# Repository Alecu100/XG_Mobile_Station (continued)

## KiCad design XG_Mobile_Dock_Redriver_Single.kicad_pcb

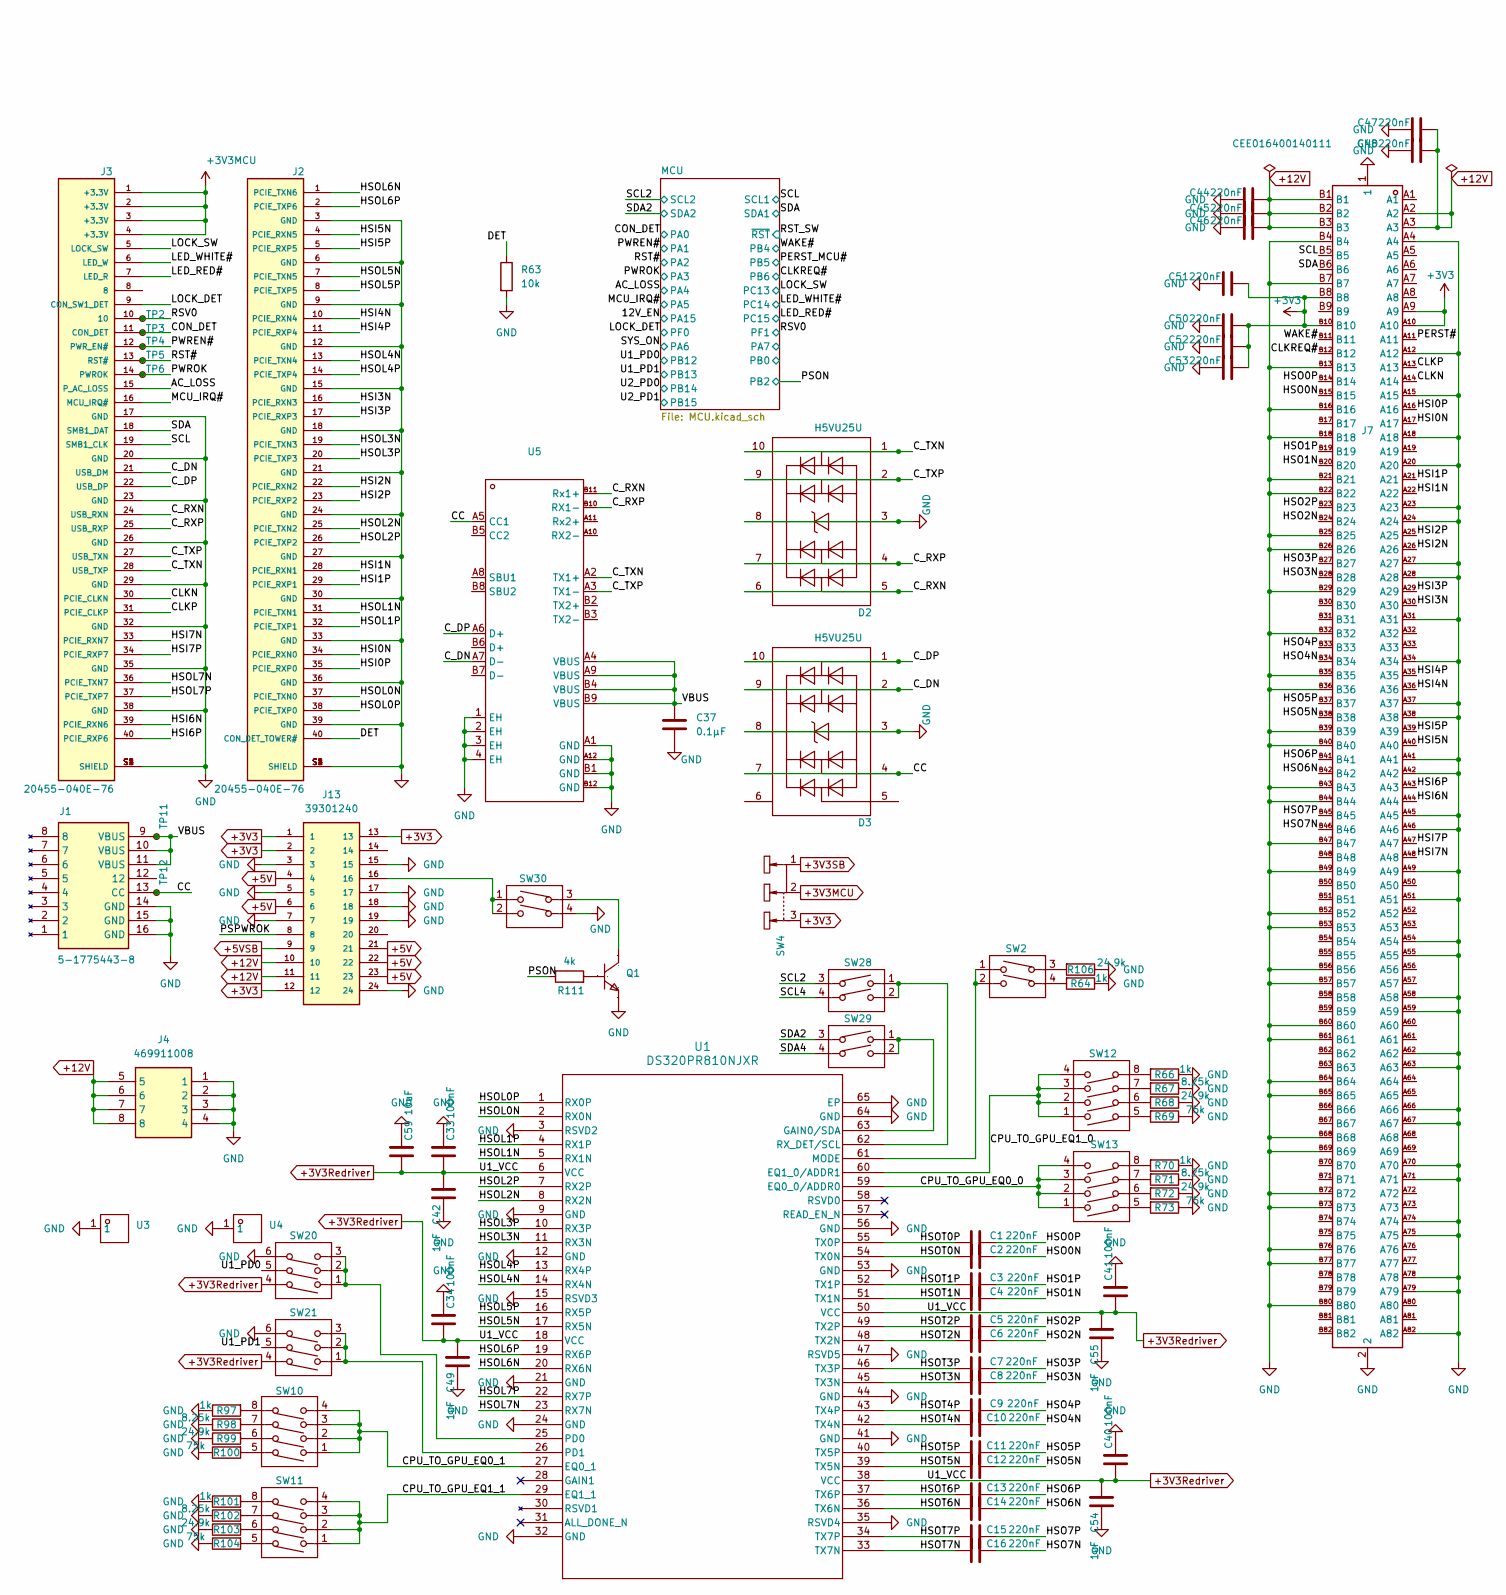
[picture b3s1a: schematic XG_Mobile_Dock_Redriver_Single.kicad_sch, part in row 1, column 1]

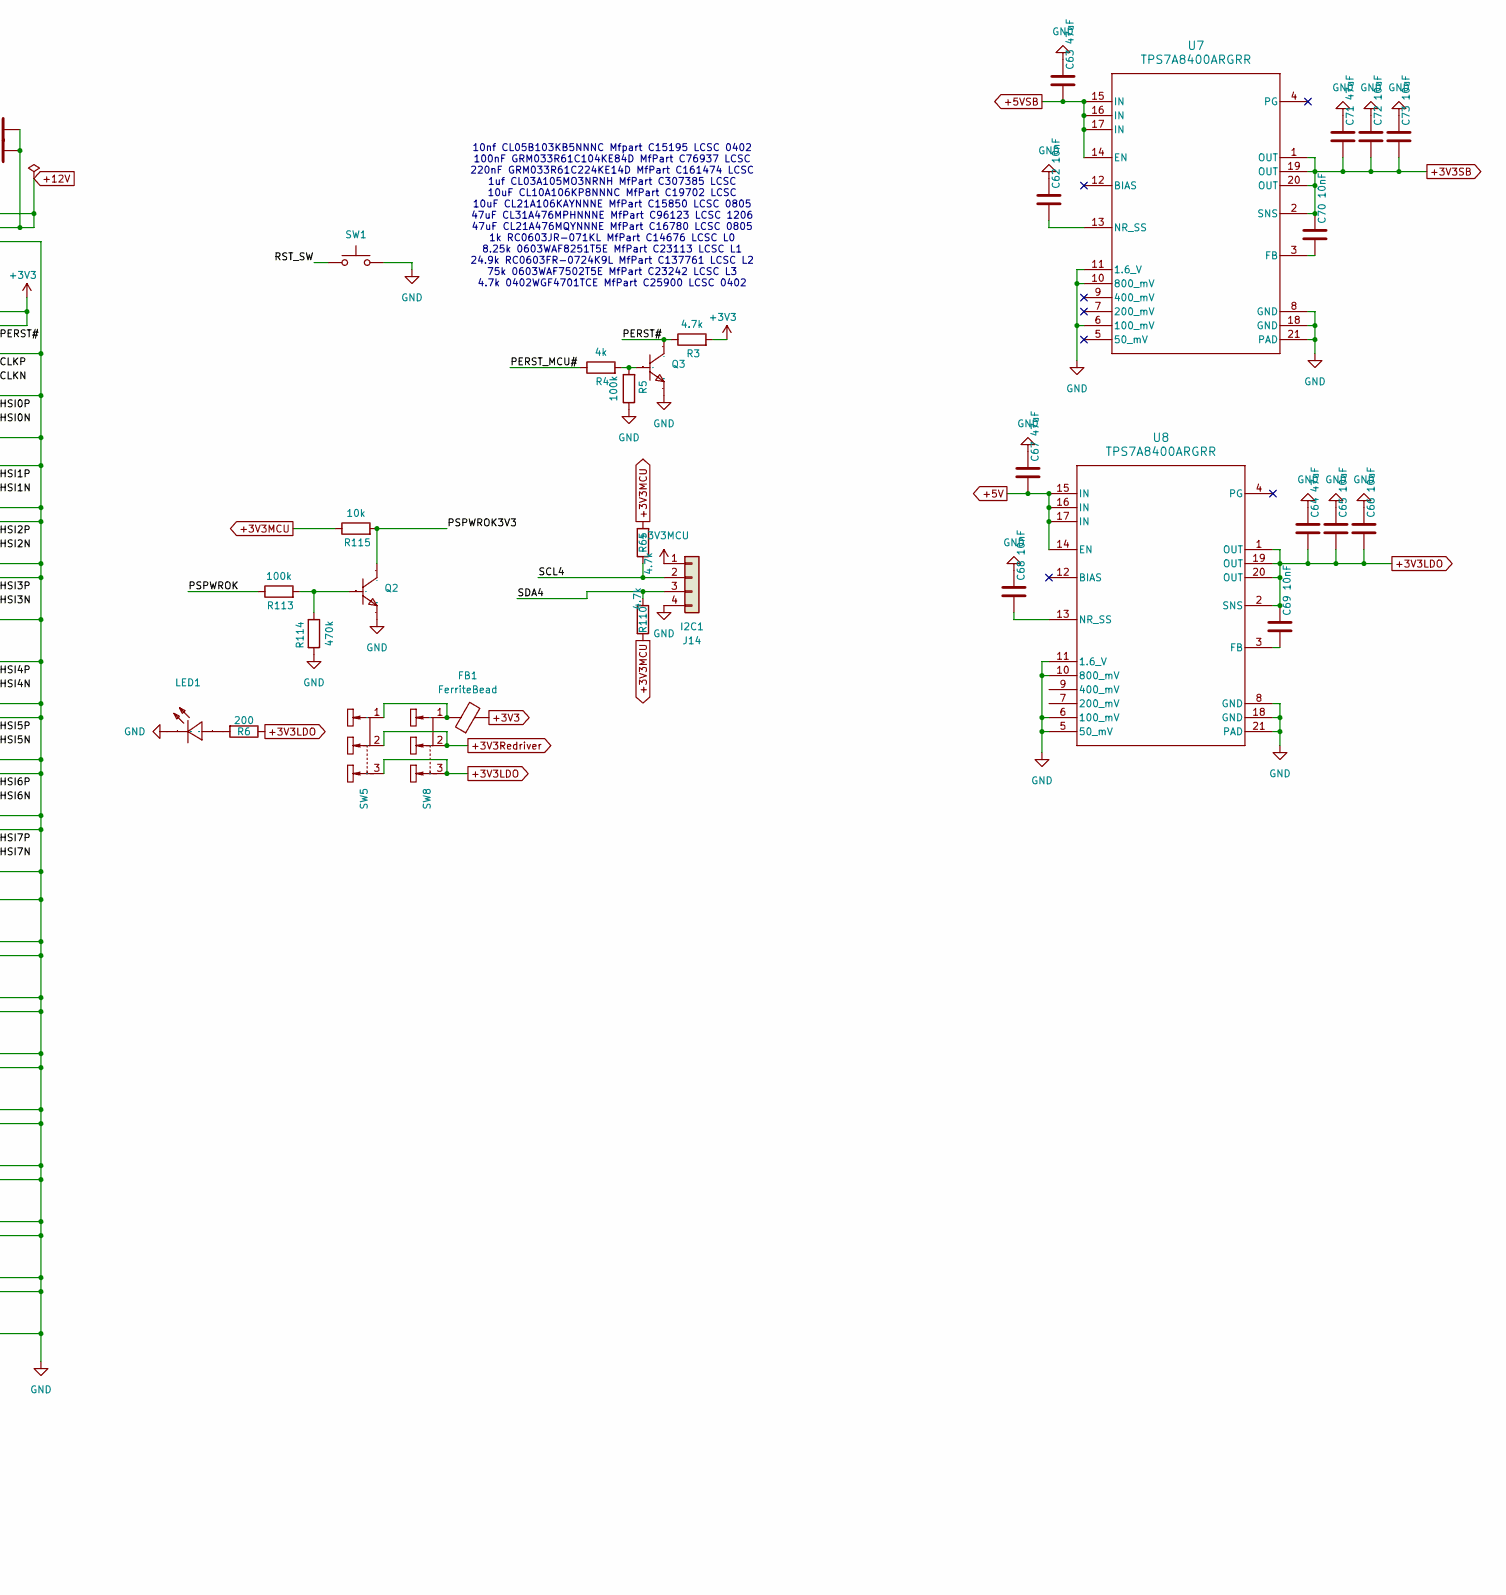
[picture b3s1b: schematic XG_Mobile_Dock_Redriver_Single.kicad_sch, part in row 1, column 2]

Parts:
C1, C2, C3, C4, C5, C6, C7, C8, C9, C10, C11, C12, C13, C14, C15, C16, C44, C45, C46, C47, C48, C50, C51, C52, C53: 220nF; C_0201_0603Metric; Part_Number GRM033R61C224KE14D; LCSC C161474
C33, C34, C40, C41: 100nF; C_0201_0603Metric; Part_Number GRM033R61C104KE84D; LCSC C76937
C37: 0.1μF; C_0402_1005Metric; Part_Number CL05B104KO5NNNC; LCSC C1525
C42, C49, C54, C55: 1uF; C_0201_0603Metric; Part_Number CL03A105MO3NRNH; LCSC C307385
C59: 10uF; C_0603_1608Metric; Part_Number CL10A106KP8NNNC; LCSC C19702
C62, C68, C69, C70: 10nF; C_0402_1005Metric; Part_Number CL05B103KB5NNNC; LCSC C15195
C63, C64, C67, C71: 47uF; C_0805_2012Metric; Part_Number CL21A476MQYNNNE; LCSC C16780
C65, C66, C72, C73: 10uF; C_0805_2012Metric; Part_Number CL21A106KAYNNNE; LCSC C15850
D2, D3: H5VU25U; AZ1045-04F; Part_Number H5VU25U; LCSC C7420374
FB1: FerriteBead; R_1206_3216Metric; Part_Number FBMJ3216HS800-TV; LCSC C2661525
J1: 5-1775443-8; Manufacturer_Part_Number 5-1775443-8
J2, J3: 20455-040E-76; Part_Number 20455-040E-76; LCSC C5160883
J4: 469911008; CON_469911008; Part_Number 469911008; LCSC C17470577
J7: CEE016400140111; CONN-SMD_164P-P1.00-CEE016400140111; PARTREV C; LCSC C4762196
J13: 39301240; CON_39300240; Part_Number 39301240; LCSC C492347
J14: I2C1; PinHeader_1x04_P2.54mm_Vertical; Part_Number 2.54-1*4; LCSC C5116483
LED1: LED0603-RD; Manufacturer Part KT-0603R; LCSC Part Name 0603 红灯 高亮
Q1, Q2, Q3: SOT-23-3_L2.9-W1.3-P1.90-LS2.4-BR; Part_Number MMBT5551(RANGE:200-300); LCSC C2145
R3, R65, R110: 4.7k; R_0402_1005Metric; Part_Number 0402WGF4701TCE; LCSC C25900
R4, R111: 4k; R_0603_1608Metric; Part_Number 0603WAF4021T5E; LCSC C23040
R5, R113: 100k; R_0603_1608Metric; Part_Number 0603WAF1003T5E; LCSC C25803
R6: 200; R_0603_1608Metric; Part_Number 0603WAF2000T5E; LCSC C8218
R63: 10k; R_0402_1005Metric; Part_Number 0402WGF1002TCE; LCSC C25744
R64, R66, R70, R97, R101: 1k; R_0603_1608Metric; Part_Number RC0603JR-071KL; LCSC C14676
R67, R71, R98, R102: 8.25k; R_0603_1608Metric; Part_Number 0603WAF8251T5E; LCSC C23113
R68, R72, R99, R103, R106: 24.9k; R_0603_1608Metric; Part_Number 0603WAF8251T5E; LCSC C137761
R69, R73, R100, R104: 75k; R_0603_1608Metric; Part_Number 0603WAF8251T5E; LCSC C23242
R114: 470k; R_0603_1608Metric; Part_Number 0603WAF4703T5E; LCSC C23178
R115: 10k; R_0603_1608Metric; Part_Number 0603WAF1002T5E; LCSC C25804
SW1: SW_Push; SW_SPST_SKQG_WithStem; Part_Number TS-1187A-B-A-B; LCSC C318884
SW2, SW28, SW29, SW30: SW-TH_DSWB02LHGET; Part_Number DSWB02LHGET; LCSC C99421
SW4, SW5, SW8: SW-TH_SS-12D10L5; Part_Number SS-12D10L5; LCSC C319012
SW10, SW11, SW12, SW13: SW-TH_DSWB04LHGET; Part_Number DSWB04LHGET; LCSC C99418
SW20, SW21: SW-TH_DSWB03LHGET; Part_Number DSWB03LHGET; LCSC C99420
TP2, TP3, TP4, TP5, TP6, TP11, TP12: TestPoint_Small; TestPoint_Pad_D1.0mm
U1: DS320PR810NJXR; WQFN-64-NJX_TEX; Part_Number DS320PR810NJXR; LCSC C6539577
U3, U4: CONN-SMD_T31000; Part_Number T31000; LCSC C481468
U5: USB-C-SMD_GT-USB-7091A; Part_Number GT-USB-7091A; LCSC C3019707
U7, U8: TPS7A8400ARGRR; RGR0020A; Part_Number TPS7A8400ARGRR; LCSC C524802

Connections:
+3V3: C50.1, C51.1, C52.1, C53.1, FB1.2, J7.A9, J7.A10, J7.B8, J7.B10, J13.1, J13.2, J13.12, J13.13, R3.2, SW4.3
+3V3LDO: C64.2, C65.2, C66.2, C69.1, R6.1, SW5.3, SW8.3, U8.1 (OUT), U8.2 (SNS), U8.19 (OUT), U8.20 (OUT)
+3V3MCU: J3.1 (+3.3V), J3.2 (+3.3V), J3.3 (+3.3V), J3.4 (+3.3V), J14.1, R65.2, R110.2, R115.1, SW4.2; also elsewhere on the board
+3V3Redriver: C33.2, C34.2, C40.2, C41.2, C42.2, C49.2, C54.2, C55.2, C59.2, SW5.2, SW8.2, SW20.4, SW21.4, U1.6 (VCC), U1.18 (VCC), U1.38 (VCC), U1.50 (VCC)
+3V3SB: C70.1, C71.2, C72.2, C73.2, SW4.1, U7.1 (OUT), U7.2 (SNS), U7.19 (OUT), U7.20 (OUT)
+5V: C67.2, J13.4, J13.6, J13.21, J13.22, J13.23, U8.14 (EN), U8.15 (IN), U8.16 (IN), U8.17 (IN)
+5VSB: C63.2, J13.9, U7.14 (EN), U7.15 (IN), U7.16 (IN), U7.17 (IN)
+12V: C44.1, C45.1, C46.1, C47.1, C48.1, J4.5, J4.6, J4.7, J4.8, J7.A2, J7.A3, J7.B1, J7.B2, J7.B3, J13.10, J13.11; also elsewhere on the board
/AC_LOSS: J3.15 (P_AC_LOSS); also elsewhere on the board
/CC: D3.4 (I/O_3), D3.7 (NC), J1.13 (CC), TP12.1, U5.A5 (CC1)
/CLKN: J3.30 (PCIE_CLKN), J7.A14
/CLKP: J3.31 (PCIE_CLKP), J7.A13
/CLKREQ#: J7.B12; also elsewhere on the board
/CON_DET: J3.11 (CON_DET), TP3.1; also elsewhere on the board
/CPU_TO_GPU_EQ0_0: SW13.1, SW13.2, SW13.3, SW13.4, U1.59 (EQ0_0/ADDR0)
/CPU_TO_GPU_EQ0_1: SW10.1, SW10.2, SW10.3, SW10.4, U1.27 (EQ0_1)
/CPU_TO_GPU_EQ1_0: SW12.1, SW12.2, SW12.3, SW12.4, U1.60 (EQ1_0/ADDR1)
/CPU_TO_GPU_EQ1_1: SW11.1, SW11.2, SW11.3, SW11.4, U1.29 (EQ1_1)
/C_DN: D3.2 (I/O_2), D3.9 (NC), J3.21 (USB_DM), U5.A7 (D-)
/C_DP: D3.1 (I/O_1), D3.10 (NC), J3.22 (USB_DP), U5.A6 (D+)
/C_RXN: D2.5 (I/O_4), D2.6 (NC), J3.24 (USB_RXN), U5.B11 (Rx1+)
/C_RXP: D2.4 (I/O_3), D2.7 (NC), J3.25 (USB_RXP), U5.B10 (RX1-)
/C_TXN: D2.1 (I/O_1), D2.10 (NC), J3.28 (USB_TXP), U5.A2 (TX1+)
/C_TXP: D2.2 (I/O_2), D2.9 (NC), J3.27 (USB_TXN), U5.A3 (TX1-)
/DET: J2.40 (CON_DET_TOWER#), R63.1
/HSI0N: J2.34 (PCIE_RXN0), J7.A17
/HSI0P: J2.35 (PCIE_RXP0), J7.A16
/HSI1N: J2.28 (PCIE_RXN1), J7.A22
/HSI1P: J2.29 (PCIE_RXP1), J7.A21
/HSI2N: J2.22 (PCIE_RXN2), J7.A26
/HSI2P: J2.23 (PCIE_RXP2), J7.A25
/HSI3N: J2.16 (PCIE_RXN3), J7.A30
/HSI3P: J2.17 (PCIE_RXP3), J7.A29
/HSI4N: J2.10 (PCIE_RXN4), J7.A36
/HSI4P: J2.11 (PCIE_RXP4), J7.A35
/HSI5N: J2.4 (PCIE_RXN5), J7.A40
/HSI5P: J2.5 (PCIE_RXP5), J7.A39
/HSI6N: J3.39 (PCIE_RXN6), J7.A44
/HSI6P: J3.40 (PCIE_RXP6), J7.A43
/HSI7N: J3.33 (PCIE_RXN7), J7.A48
/HSI7P: J3.34 (PCIE_RXP7), J7.A47
/HSO0N: C2.1, J7.B15
/HSO0P: C1.1, J7.B14
/HSO1N: C4.1, J7.B20
/HSO1P: C3.1, J7.B19
/HSO2N: C6.1, J7.B24
/HSO2P: C5.1, J7.B23
/HSO3N: C8.1, J7.B28
/HSO3P: C7.1, J7.B27
/HSO4N: C10.1, J7.B34
/HSO4P: C9.1, J7.B33
/HSO5N: C12.1, J7.B38
/HSO5P: C11.1, J7.B37
/HSO6N: C14.1, J7.B42
/HSO6P: C13.1, J7.B41
/HSO7N: C16.1, J7.B46
/HSO7P: C15.1, J7.B45
/HSOL0N: J2.37 (PCIE_TXN0), U1.2 (RX0N)
/HSOL0P: J2.38 (PCIE_TXP0), U1.1 (RX0P)
/HSOL1N: J2.31 (PCIE_TXN1), U1.5 (RX1N)
/HSOL1P: J2.32 (PCIE_TXP1), U1.4 (RX1P)
/HSOL2N: J2.25 (PCIE_TXN2), U1.8 (RX2N)
/HSOL2P: J2.26 (PCIE_TXP2), U1.7 (RX2P)
/HSOL3N: J2.19 (PCIE_TXN3), U1.11 (RX3N)
/HSOL3P: J2.20 (PCIE_TXP3), U1.10 (RX3P)
/HSOL4N: J2.13 (PCIE_TXN4), U1.14 (RX4N)
/HSOL4P: J2.14 (PCIE_TXP4), U1.13 (RX4P)
/HSOL5N: J2.7 (PCIE_TXN5), U1.17 (RX5N)
/HSOL5P: J2.8 (PCIE_TXP5), U1.16 (RX5P)
/HSOL6N: J2.1 (PCIE_TXN6), U1.20 (RX6N)
/HSOL6P: J2.2 (PCIE_TXP6), U1.19 (RX6P)
/HSOL7N: J3.36 (PCIE_TXN7), U1.23 (RX7N)
/HSOL7P: J3.37 (PCIE_TXP7), U1.22 (RX7P)
/HSOT0N: C2.2, U1.54 (TX0N)
/HSOT0P: C1.2, U1.55 (TX0P)
/HSOT1N: C4.2, U1.51 (TX1N)
/HSOT1P: C3.2, U1.52 (TX1P)
/HSOT2N: C6.2, U1.48 (TX2N)
/HSOT2P: C5.2, U1.49 (TX2P)
/HSOT3N: C8.2, U1.45 (TX3N)
/HSOT3P: C7.2, U1.46 (TX3P)
/HSOT4N: C10.2, U1.42 (TX4N)
/HSOT4P: C9.2, U1.43 (TX4P)
/HSOT5N: C12.2, U1.39 (TX5N)
/HSOT5P: C11.2, U1.40 (TX5P)
/HSOT6N: C14.2, U1.36 (TX6N)
/HSOT6P: C13.2, U1.37 (TX6P)
/HSOT7N: C16.2, U1.33 (TX7N)
/HSOT7P: C15.2, U1.34 (TX7P)
/LED_RED#: J3.7 (LED_R); also elsewhere on the board
/LED_WHITE#: J3.6 (LED_W); also elsewhere on the board
/LOCK_DET: J3.9 (CON_SW1_DET); also elsewhere on the board
/LOCK_SW: J3.5 (LOCK_SW); also elsewhere on the board
/MCU_IRQ#: J3.16 (MCU_IRQ#); also elsewhere on the board
/PERST#: J7.A11, Q3.3 (C), R3.1
/PERST_MCU#: R4.1; also elsewhere on the board
/PSON: R111.1; also elsewhere on the board
/PSPWROK: J13.8, R113.1
/PSPWROK3V3: Q2.3 (C), R115.2
/PWREN#: J3.12 (PWR_EN#), TP4.1; also elsewhere on the board
/PWROK: J3.14 (PWROK), TP6.1; also elsewhere on the board
/RST#: J3.13 (RST#), TP5.1; also elsewhere on the board
/RST_SW: SW1.1; also elsewhere on the board
/RSV0: J3.10, TP2.1; also elsewhere on the board
/SCL: J3.19 (SMB1_CLK), J7.B5; also elsewhere on the board
/SCL2: SW28.3; also elsewhere on the board
/SCL4: J14.2, R65.1, SW28.4
/SDA: J3.18 (SMB1_DAT), J7.B6; also elsewhere on the board
/SDA2: SW29.3; also elsewhere on the board
/SDA4: J14.3, R110.1, SW29.4
/U1_PD0: SW20.5; also elsewhere on the board
/U1_PD1: SW21.5; also elsewhere on the board
/VBUS: C37.1, J1.9 (VBUS), J1.10 (VBUS), J1.11 (VBUS), TP11.1, U5.A4 (VBUS), U5.A9 (VBUS), U5.B4 (VBUS), U5.B9 (VBUS)
/WAKE#: J7.B11; also elsewhere on the board
GND: C33.1, C34.1, C37.2, C40.1, C41.1, C42.1, C44.2, C45.2, C46.2, C47.2, C48.2, C49.1, C50.2, C51.2, C52.2, C53.2, C54.1, C55.1, C59.1, C62.1, C63.1, C64.1, C65.1, C66.1, C67.1, C68.1, C71.1, C72.1, C73.1, D2.3 (GND), D2.8 (GND), D3.3 (GND), D3.8 (GND), J1.14 (GND), J1.15 (GND), J1.16 (GND), J2.3 (GND), J2.6 (GND), J2.9 (GND), J2.12 (GND), J2.15 (GND), J2.18 (GND), J2.21 (GND), J2.24 (GND), J2.27 (GND), J2.30 (GND), J2.33 (GND), J2.36 (GND), J2.39 (GND), J2.S1 (SHIELD), J2.S2 (SHIELD), J2.S3 (SHIELD), J2.S4 (SHIELD), J3.17 (GND), J3.20 (GND), J3.23 (GND), J3.26 (GND), J3.29 (GND), J3.32 (GND), J3.35 (GND), J3.38 (GND), J3.S1 (SHIELD), J3.S2 (SHIELD), J3.S3 (SHIELD), J3.S4 (SHIELD), J4.1, J4.2, J4.3, J4.4, J7.1, J7.2, J7.A4, J7.A12, J7.A15, J7.A18, J7.A20, J7.A23, J7.A24, J7.A27, J7.A28, J7.A31, J7.A34, J7.A37, J7.A38, J7.A41, J7.A42, J7.A45, J7.A46, J7.A49, J7.A51, J7.A54, J7.A55, J7.A58, J7.A59, J7.A62, J7.A63, J7.A66, J7.A67, J7.A70, J7.A71, J7.A74, J7.A75, J7.A78, J7.A79, J7.A82, J7.B4, J7.B7, J7.B13, J7.B16, J7.B18, J7.B21, J7.B22, J7.B25, J7.B26, J7.B29, J7.B32, J7.B35, J7.B36, J7.B39, J7.B40, J7.B43, J7.B44, J7.B47, J7.B49, J7.B52, J7.B53, J7.B56, J7.B57, J7.B60, J7.B61, J7.B64, J7.B65, J7.B68, J7.B69, J7.B72, J7.B73, J7.B76, J7.B77, J7.B80, J13.3, J13.5, J13.7, J13.15, J13.17, J13.18, J13.19, J13.24, J14.4, LED1.1 (K), Q1.2 (E), Q2.2 (E), Q3.2 (E), R5.1, R63.2, R64.1, R66.1, R67.1, R68.1, R69.1, R70.1, R71.1, R72.1, R73.1, R97.1, R98.1, R99.1, R100.1, R101.1, R102.1, R103.1, R104.1, R106.1, R114.2, SW1.2, SW20.6, SW21.6, SW30.4, U1.3 (RSVD2), U1.9 (GND), U1.12 (GND), U1.15 (RSVD3), U1.21 (GND), U1.24 (GND), U1.32 (GND), U1.35 (RSVD4), U1.41 (GND), U1.44 (GND), U1.47 (RSVD5), U1.53 (GND), U1.56 (GND), U1.64 (GND), U1.65 (EP), U3.1, U4.1, U5.1 (EH), U5.2 (EH), U5.3 (EH), U5.4 (EH), U5.A1 (GND), U5.A12 (GND), U5.B1 (GND), U5.B12 (GND), U7.6 (100_mV), U7.8 (GND), U7.10 (800_mV), U7.11 (1.6_V), U7.18 (GND), U7.21 (PAD), U8.5 (50_mV), U8.6 (100_mV), U8.8 (GND), U8.10 (800_mV), U8.11 (1.6_V), U8.18 (GND), U8.21 (PAD); also elsewhere on the board
unnamed: FB1.1, SW5.1, SW8.1
unnamed: J13.16, SW30.1, SW30.2
unnamed: LED1.2 (A), R6.2
unnamed: Q1.1 (B), R111.2
unnamed: Q1.3 (C), SW30.3
unnamed: Q2.1 (B), R113.2, R114.1
unnamed: Q3.1 (B), R4.2, R5.2
unnamed: R64.2, SW2.4
unnamed: R66.2, SW12.8
unnamed: R67.2, SW12.7
unnamed: R68.2, SW12.6
unnamed: R69.2, SW12.5
unnamed: R70.2, SW13.8
unnamed: R71.2, SW13.7
unnamed: R72.2, SW13.6
unnamed: R73.2, SW13.5
unnamed: R97.2, SW10.8
unnamed: R98.2, SW10.7
unnamed: R99.2, SW10.6
unnamed: R100.2, SW10.5
unnamed: R101.2, SW11.8
unnamed: R102.2, SW11.7
unnamed: R103.2, SW11.6
unnamed: R104.2, SW11.5
unnamed: R106.2, SW2.3
unnamed: SW29.1, SW29.2, U1.63 (GAIN0/SDA)
unnamed: SW2.1, SW2.2, U1.61 (MODE)
unnamed: SW20.1, SW20.2, SW20.3, U1.25 (PD0)
unnamed: SW21.1, SW21.2, SW21.3, U1.26 (PD1)
unnamed: SW28.1, SW28.2, U1.62 (RX_DET/SCL)
unnamed: C70.2, U7.3 (FB)
unnamed: C62.2, U7.13 (NR_SS)
unnamed: C69.2, U8.3 (FB)
unnamed: C68.2, U8.13 (NR_SS)

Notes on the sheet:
10nf CL05B103KB5NNNC Mfpart C15195 LCSC 0402 100nF GRM033R61C104KE84D MfPart C76937 LCSC 220nF GRM033R61C224KE14D MfPart C161474 LCSC 1uf CL03A105MO3NRNH MfPart C307385 LCSC 10uF CL10A106KP8NNNC MfPart C19702 LCSC 10uF CL21A106KAYNNNE MfPart C15850 LCSC 0805 47uF CL31A476MPHNNNE MfPart C96123 LCSC 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

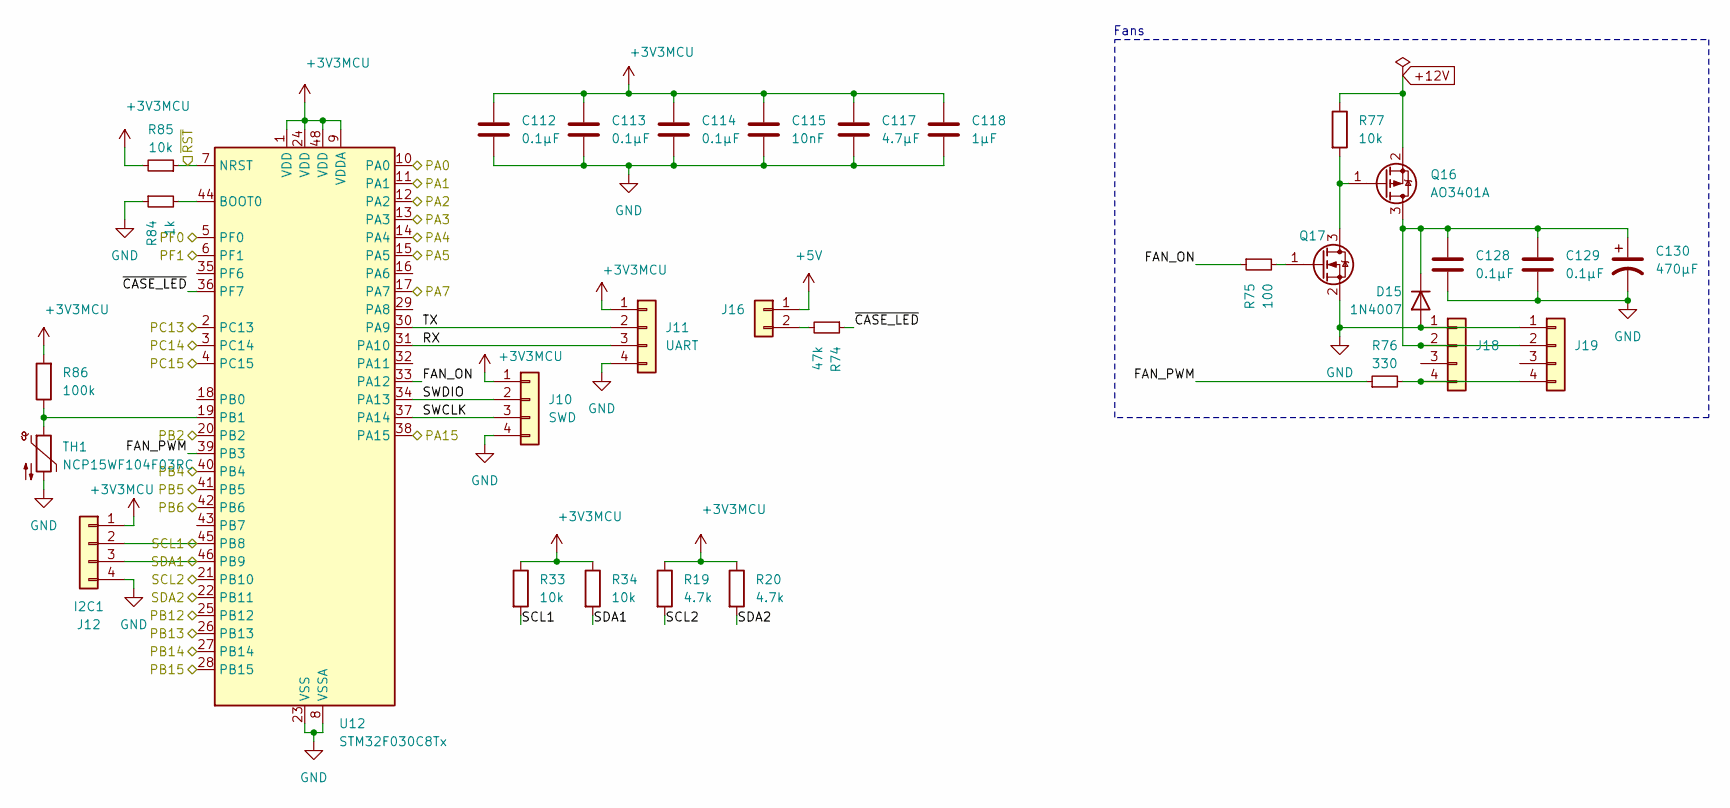
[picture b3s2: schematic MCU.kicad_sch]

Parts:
C112, C113, C114: 0.1µF; C_0402_1005Metric; Part_Number CL05B104KB54PNC; LCSC C307331
C115: 10nF; C_0402_1005Metric; Part_Number CL05B103KB5NNNC; LCSC C15195
C117: 4.7µF; C_0402_1005Metric; Part_Number CL05A475MP5NRNC; LCSC C23733
C118: 1µF; C_0402_1005Metric; Part_Number CL05A105KA5NQNC; LCSC C52923
C128, C129: 0.1µF; C_0603_1608Metric; Part_Number CC0603KRX7R9BB104; LCSC C14663
C130: 470µF; CP_Radial_D10.0mm_P5.00mm; Part_Number EGT477M1HG16RRS0P; LCSC C3015599
D15: 1N4007; D_SOD-123F; Part_Number 1N4007W; LCSC C18199088
J10: SWD; PinHeader_1x04_P2.54mm_Vertical; Part_Number 2.54-1*4; LCSC C5116483
J11: UART; PinHeader_1x04_P2.54mm_Vertical; Part_Number 2.54-1*4; LCSC C5116483
J12: I2C1; PinHeader_1x04_P2.54mm_Vertical; Part_Number 2.54-1*4; LCSC C5116483
J16: JST_PH_S2B-PH-K_1x02_P2.00mm_Horizontal; Part_Number S2B-PH-KL(LF)(SN); LCSC C160237
J18, J19: CONN_SD-47053-001_H10p00_MOL; Part_Number 470531000; LCSC C240840
Q16: AO3401A; SOT-23; Part_Number AO3401A; LCSC C15127
Q17: 2N7002W; SOT-323-3_L2.0-W1.3-P1.30-LS2.1-BR; Part_Number 2N7002W; LCSC C7420322
R19, R20: 4.7k; R_0402_1005Metric; Part_Number 0402WGF4701TCE; LCSC C25900
R33, R34, R77, R85: 10k; R_0402_1005Metric; Part_Number 0402WGF1002TCE; LCSC C25744
R74: 47k; R_0402_1005Metric; Part_Number 0402WGF4702TCE; LCSC C25792
R75: 100; R_0402_1005Metric; Part_Number 0402WGF1000TCE; LCSC C25076
R76: 330; R_0402_1005Metric; Part_Number 0402WGF3300TCE; LCSC C25104
R84: 1k; R_0402_1005Metric; Part_Number 0402WGF1001TCE; LCSC C11702
R86: 100k; R_0402_1005Metric; Part_Number 0402WGF1003TCE; LCSC C25741
TH1: NCP15WF104F03RC; R_0402_1005Metric; Part_Number NCP15WF104F03RC; LCSC C77130
U12: STM32F030C8Tx; LQFP-48_7x7mm_P0.5mm; Part_Number STM32F030C8T6; LCSC C23922

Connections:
+3V3MCU: C112.1, C113.1, C114.1, C115.1, C117.1, C118.1, J10.1, J11.1, J12.1, R19.1, R20.1, R33.1, R34.1, R85.2, R86.2, U12.1 (VDD), U12.9 (VDDA), U12.24 (VDD), U12.48 (VDD); also elsewhere on the board
+12V: Q16.2 (S), R77.1; also elsewhere on the board
/12V_EN: U12.38 (PA15)
/AC_LOSS: U12.14 (PA4); also elsewhere on the board
/CLKREQ#: U12.42 (PB6); also elsewhere on the board
/CON_DET: U12.10 (PA0); also elsewhere on the board
/LED_RED#: U12.4 (PC15); also elsewhere on the board
/LED_WHITE#: U12.3 (PC14); also elsewhere on the board
/LOCK_DET: U12.5 (PF0); also elsewhere on the board
/LOCK_SW: U12.2 (PC13); also elsewhere on the board
/MCU/FAN_ON: R75.1, U12.33 (PA12)
/MCU/FAN_PWM: R76.1, U12.39 (PB3)
/MCU/PA7: U12.17 (PA7)
/MCU/RX: J11.3, U12.31 (PA10)
/MCU/SWCLK: J10.3, U12.37 (PA14)
/MCU/SWDIO: J10.2, U12.34 (PA13)
/MCU/TX: J11.2, U12.30 (PA9)
/MCU/~CASE_LED: R74.1, U12.36 (PF7)
/MCU_IRQ#: U12.15 (PA5); also elsewhere on the board
/PERST_MCU#: U12.41 (PB5); also elsewhere on the board
/PSON: U12.20 (PB2); also elsewhere on the board
/PWREN#: U12.11 (PA1); also elsewhere on the board
/PWROK: U12.13 (PA3); also elsewhere on the board
/RST#: U12.12 (PA2); also elsewhere on the board
/RST_SW: R85.1, U12.7 (NRST); also elsewhere on the board
/RSV0: U12.6 (PF1); also elsewhere on the board
/SCL: J12.2, R33.2, U12.45 (PB8); also elsewhere on the board
/SCL2: R19.2, U12.21 (PB10); also elsewhere on the board
/SDA: J12.3, R34.2, U12.46 (PB9); also elsewhere on the board
/SDA2: R20.2, U12.22 (PB11); also elsewhere on the board
/U1_PD0: U12.25 (PB12); also elsewhere on the board
/U1_PD1: U12.26 (PB13); also elsewhere on the board
/U2_PD0: U12.27 (PB14)
/U2_PD1: U12.28 (PB15)
/WAKE#: U12.40 (PB4); also elsewhere on the board
GND: C112.2, C113.2, C114.2, C115.2, C117.2, C118.2, C128.2, C129.2, C130.2, D15.2 (A), J10.4, J11.4, J12.4, J18.1, J19.1, Q17.2 (S), R84.1, TH1.2, U12.8 (VSSA), U12.23 (VSS), U12.47 (VSS); also elsewhere on the board
unnamed: C128.1, C129.1, C130.1, D15.1 (K), J18.2, J19.2, Q16.3 (D)
unnamed: J16.2, R74.2
unnamed: J18.4, J19.4, R76.2
unnamed: Q16.1 (G), Q17.3 (D), R77.2
unnamed: Q17.1 (G), R75.2
unnamed: R84.2, U12.44 (BOOT0)
unnamed: R86.1, TH1.1, U12.19 (PB1)

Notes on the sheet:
Fans

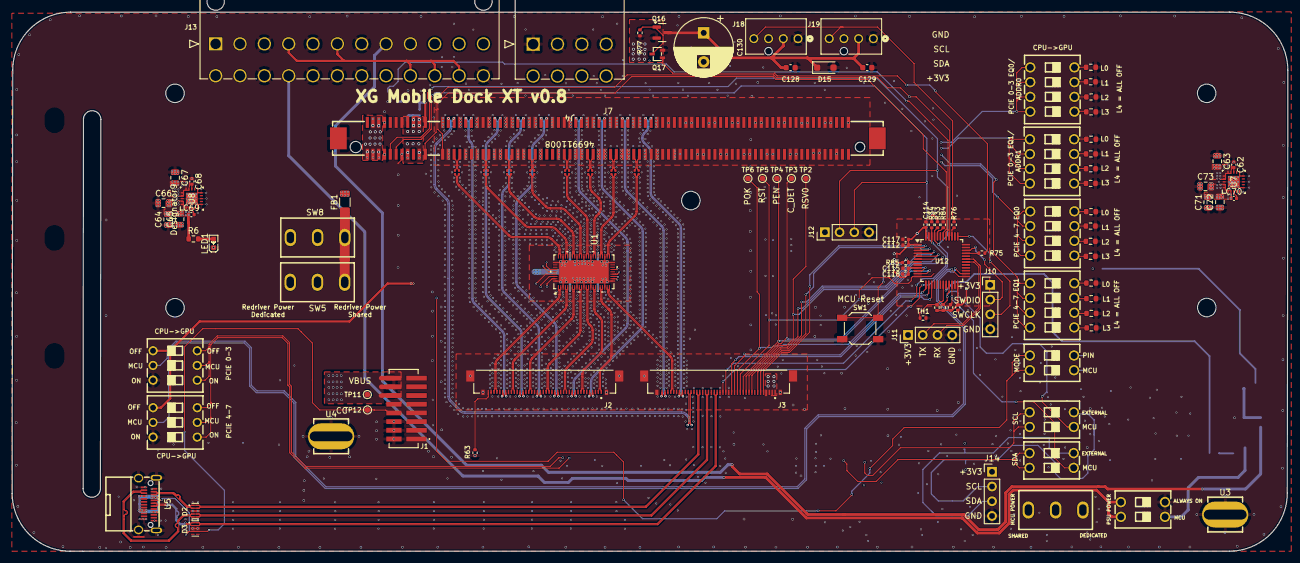
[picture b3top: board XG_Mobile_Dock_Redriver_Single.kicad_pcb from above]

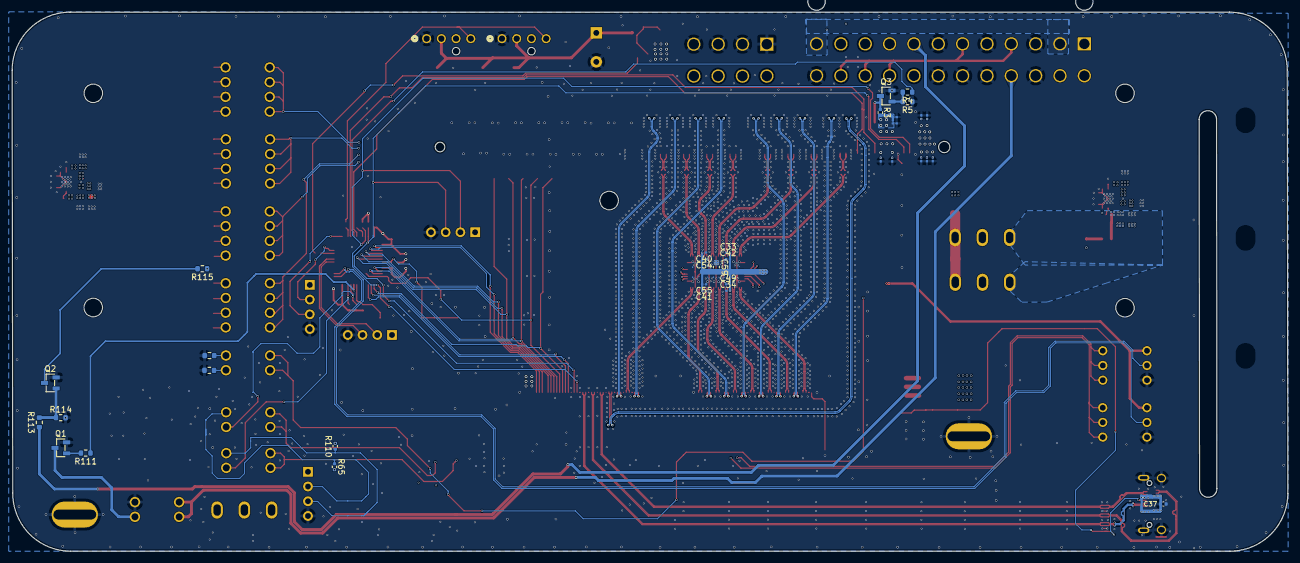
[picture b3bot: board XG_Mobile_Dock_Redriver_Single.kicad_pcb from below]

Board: 6 copper layers, 220.1 x 93.0 mm, 146 parts (33 on the bottom side), 161 nets.
